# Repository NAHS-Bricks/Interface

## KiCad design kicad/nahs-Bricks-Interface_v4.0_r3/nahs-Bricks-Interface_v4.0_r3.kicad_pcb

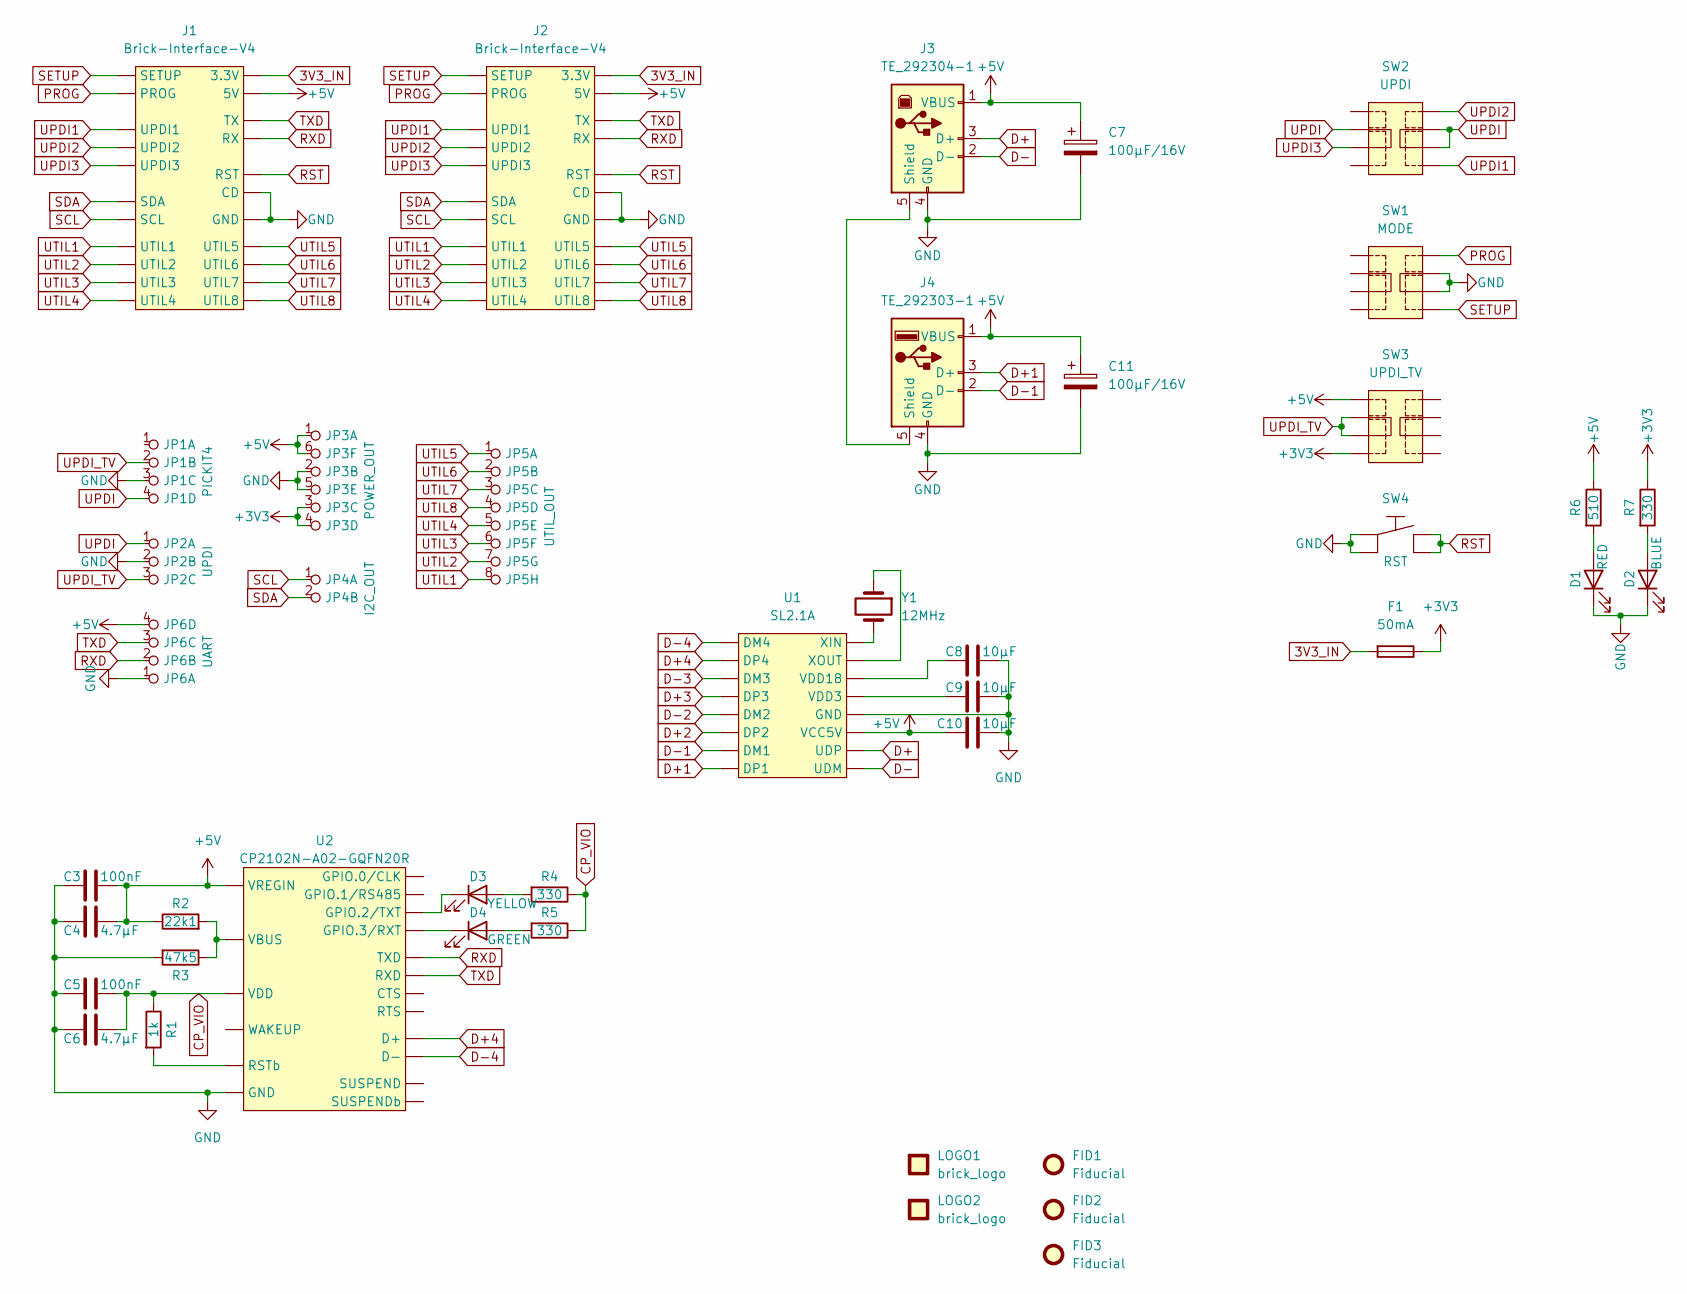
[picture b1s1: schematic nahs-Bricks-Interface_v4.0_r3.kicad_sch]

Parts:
C3, C5: 100nF; C_0805_2012Metric
C4, C6: 4.7µF; C_0805_2012Metric
C7, C11: 100µF/16V; CP_Elec_5x5.4
C8, C9, C10: 10µF; C_0805_2012Metric
D1: RED; LED_0805_2012Metric
D2: BLUE; LED_0805_2012Metric
D3: YELLOW; LED_0805_2012Metric
D4: GREEN; LED_0805_2012Metric
F1: 50mA; Fuse_1206_3216Metric
FID1, FID2, FID3: Fiducial; Fiducial_1mm_Mask2mm
J1: Brick-Interface-V4; Brick_Interface_V4_iside
J2: Brick-Interface-V4; Brick_Interface_V4_iside_straddle
J3: TE_292304-1; USB_B_OST_USB-B1HSxx_Horizontal
J4: TE_292303-1; USB_A_Stewart_SS-52100-001_Horizontal
JP1, JP6: PINHD_1X04; PINHD_1X04_2.54_1mm_Round
JP2: PINHD_1X03; PINHD_1X03_2.54_1mm_Round
JP3: PINHD_2X03; PINHD_2X03_2.54_1mm_Round
JP4: PINHD_1x02; PINHD_1X02_2.54_1mm_Round
JP5: PINHD_2X04; PINHD_2X04_2.54_1mm_Round
LOGO1: brick_logo; x8mm
LOGO2: brick_logo; x17mm
R1: 1k; R_0805_2012Metric
R2: 22k1; R_0805_2012Metric
R3: 47k5; R_0805_2012Metric
R4, R5, R7: 330; R_0603_1608Metric
R6: 510; R_0603_1608Metric
SW1, SW2, SW3: K3-2336S-F1
SW4: Taster_4545
U1: SL2.1A; SOP-16_3.9x9.9mm_P1.27mm
U2: CP2102N-A02-GQFN20R; QFN20
Y1: 12MHz; Crystal_SMD_HC49-SD

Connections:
3V3_IN: F1.2, J1.B11 (3.3V), J2.B11 (3.3V)
+3V3: F1.1, JP3.3, JP3.4, R7.1, SW3.4
+5V: C3.2, C4.2, C7.1, C10.1, C11.1, J1.B15 (5V), J1.B16 (5V), J1.B17 (5V), J1.B18 (5V), J2.B15 (5V), J2.B16 (5V), J2.B17 (5V), J2.B18 (5V), J3.1 (VBUS), J4.1 (VBUS), JP3.1, JP3.6, JP6.4, R2.1, R6.1, SW3.1, U1.11 (VCC5V), U2.7 (VREGIN)
CP_VIO: C5.2, C6.2, R1.1, R4.1, R5.1, U2.6 (VDD)
D+: J3.3 (D+), U1.10 (UDP)
D+1: J4.3 (D+), U1.8 (DP1)
D+2: U1.6 (DP2)
D+3: U1.4 (DP3)
D+4: U1.2 (DP4), U2.4 (D+)
D-: J3.2 (D-), U1.9 (UDM)
D-1: J4.2 (D-), U1.7 (DM1)
D-2: U1.5 (DM2)
D-3: U1.3 (DM3)
D-4: U1.1 (DM4), U2.5 (D-)
GND: C3.1, C4.1, C5.1, C6.1, C7.2, C8.2, C9.2, C10.2, C11.2, D1.1 (K), D2.1 (K), J1.A14 (CD), J1.A15 (GND), J1.A16 (GND), J1.A17 (GND), J1.A18 (GND), J2.A14 (CD), J2.A15 (GND), J2.A16 (GND), J2.A17 (GND), J2.A18 (GND), J3.4 (GND), J4.4 (GND), JP1.3, JP2.2, JP3.2, JP3.5, JP6.1, R3.2, SW1.6, SW1.7, SW4.1, SW4.2, U1.12 (GND), U2.3 (GND), U2.12 (GND), U2.21 (GND)
unnamed: C8.1, U1.14 (VDD18)
unnamed: C9.1, U1.13 (VDD3)
unnamed: D1.2 (A), R6.2
unnamed: D2.2 (A), R7.2
unnamed: D3.1 (K), U2.20 (GPIO.2/TXT)
unnamed: D3.2 (A), R4.2
unnamed: D4.1 (K), U2.19 (GPIO.3/RXT)
unnamed: D4.2 (A), R5.2
unnamed: J3.5 (Shield), J4.5 (Shield)
unnamed: R1.2, U2.9 (RSTb)
unnamed: R2.2, R3.1, U2.8 (VBUS)
unnamed: U1.15 (XOUT), Y1.1
unnamed: U1.16 (XIN), Y1.2
PROG: J1.B12 (PROG), J2.B12 (PROG), SW1.8
RST: J1.B14 (RST), J2.B14 (RST), SW4.3, SW4.4
RXD: J1.A12 (RX), J2.A12 (RX), JP6.2, U2.18 (TXD)
SCL: J1.A9 (SCL), J2.A9 (SCL), JP4.1
SDA: J1.B9 (SDA), J2.B9 (SDA), JP4.2
SETUP: J1.B13 (SETUP), J2.B13 (SETUP), SW1.5
TXD: J1.A13 (TX), J2.A13 (TX), JP6.3, U2.17 (RXD)
UPDI: JP1.4, JP2.1, SW2.2, SW2.6, SW2.7
UPDI1: J1.A11 (UPDI1), J2.A11 (UPDI1), SW2.5
UPDI2: J1.A10 (UPDI2), J2.A10 (UPDI2), SW2.8
UPDI3: J1.B10 (UPDI3), J2.B10 (UPDI3), SW2.3
UPDI_TV: JP1.2, JP2.3, SW3.2, SW3.3
UTIL1: J1.B1 (UTIL1), J2.B1 (UTIL1), JP5.8
UTIL2: J1.B2 (UTIL2), J2.B2 (UTIL2), JP5.7
UTIL3: J1.B3 (UTIL3), J2.B3 (UTIL3), JP5.6
UTIL4: J1.B4 (UTIL4), J2.B4 (UTIL4), JP5.5
UTIL5: J1.A1 (UTIL5), J2.A1 (UTIL5), JP5.1
UTIL6: J1.A2 (UTIL6), J2.A2 (UTIL6), JP5.2
UTIL7: J1.A3 (UTIL7), J2.A3 (UTIL7), JP5.3
UTIL8: J1.A4 (UTIL8), J2.A4 (UTIL8), JP5.4

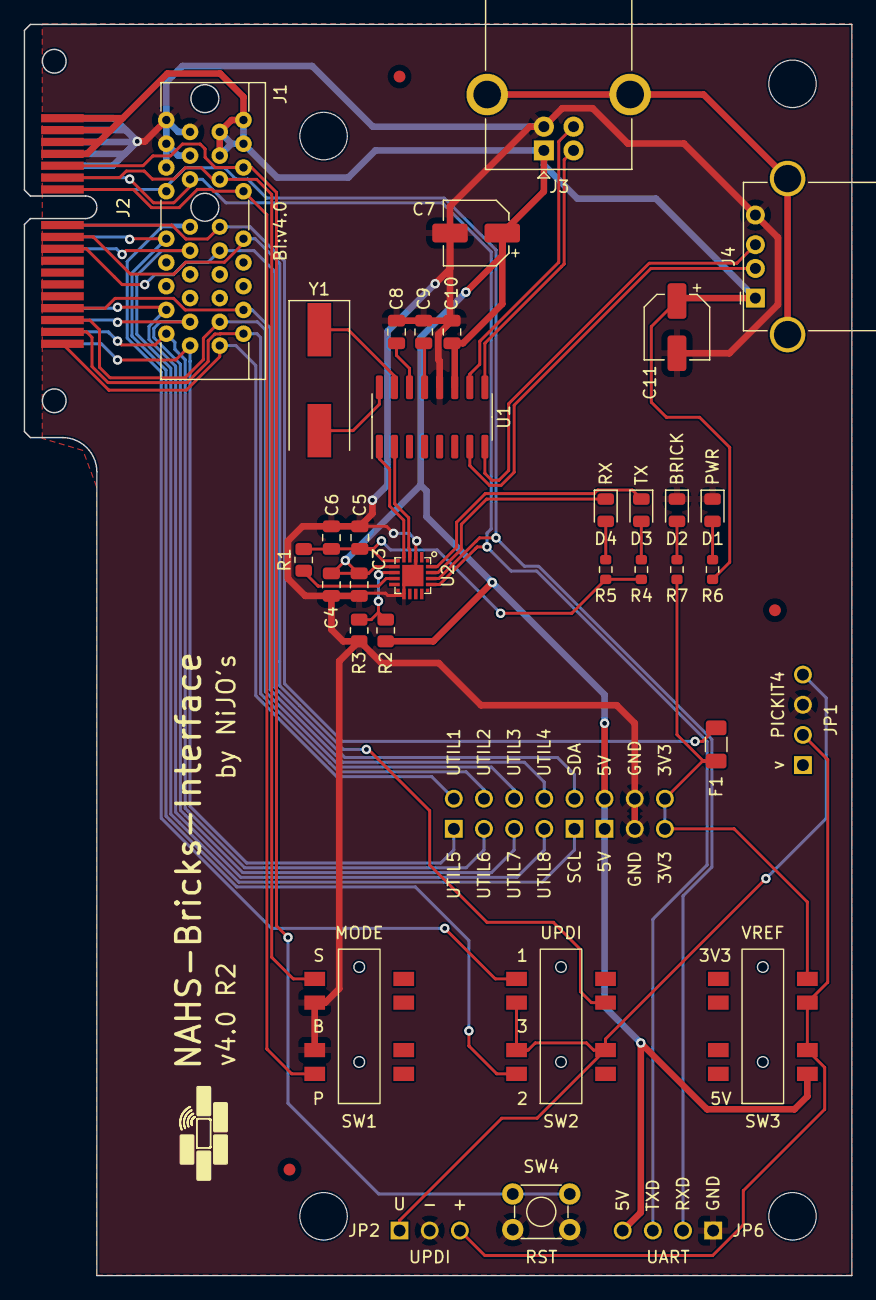
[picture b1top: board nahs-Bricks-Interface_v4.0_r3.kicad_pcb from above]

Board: 2 copper layers, 69.7 x 105.4 mm, 43 parts (1 on the bottom side), 44 nets.

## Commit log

2021-01-14 basic design and routing done
2021-01-16 routing done
2021-01-17 added planes
2021-01-19 Finale Version v1.0_r1 die an JLCPCB übermittelt wurde
2021-02-18 v1.0 R2 board vorbereitet
2021-05-08 v2.0_r1 Board Design
2021-05-11 added third UPDI Pin
2021-05-14 cleaned version of brick interface
2021-07-22 board v3.0 r1 designed
2021-10-04 board v3.0 r2 designed
2022-09-11 v4.0 r1 should be done
2023-11-16 v4.0 r1 Board done
2023-11-16 added LICENSE
2023-11-16 added zip files to be ignored
2023-11-21 v4.0 r2 Board done
2023-11-22 v4.0 r2 ibom done
2023-12-03 changed colors of LEDs
2024-02-22 v4.0 r3 Board started - had swapped pins on UPDI header
